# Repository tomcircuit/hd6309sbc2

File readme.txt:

This information pertains to the HD6309 Singleboard Computer v2.0

The HD6309 SBC II is a retroputing distraction, motivated by the fun I had designing
and using my first HD6309 SBC project. This time around, I favored 'all mod cons' over
'old skool'. In contrast to the v1.0, this version loses the Zilog SCC and Zilog CIO
devices, expands RAM to 16MB and addressable ROM to 64K. The SD card interface is
retained, as is the more up-to-date I2C realtime clock. The heart of this SBC is an
Altera Cyclone IV FPGA, in which all of the glue logic and peripherals are implemented.
So, with vastly more logic capacity, easy to do UARTs, the SPI master, a more friendly
I2C master, a paged memory mapper, and whatever else springs to mind...  The 
'penalty' for this luxury is that of mixed voltage design - the CPU and clock signals 
are in a 5V domain, everything else is in the 3.3V domain. A 5V DC/DC supplies the
CPU. Four octal transceivers shift the TTL signalling to LV-TTL. Sure, I could have 
put the CPU core in the FPGA, but no CPU just seems a bit like 'cheating'.
LOL, to each their own :-)  The SBC v2 is also physically smaller than its v1.0 
predecessor; measures 100 x 120mm.

I devised a stacking 64-pin connector scheme so that the FPGA board, the CPU board,
and an I/O board can all be used together. I have also spec'd out a 65C816 CPU board,
and a MC68HC000 board.

Firmware wise, I'll keep the rudimentary monitor, NoICE support, and the ROM-resident 
6809 MICROSOFT BASIC interpreter which I implemented on v1.0 (the latter is courtesty 
of Grant Searle). 

More up-to-date information on the SBC can be found on the Hackaday project page:
https://hackaday.io/project/173401-hd6309-singleboard-computer-ii

This work is licensed under the Creative Commons Attribution-ShareAlike 4.0 International License. 
To view a copy of this license, visit http://creativecommons.org/licenses/by-sa/4.0/.

HD6309 Singleboard Computer II
Tom LeMense
9/17/2024

tomcircuit@gmail.com
@TomLeMense

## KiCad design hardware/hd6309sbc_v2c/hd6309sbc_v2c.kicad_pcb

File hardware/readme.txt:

This set of design files implements the Schematic and PCB for the HD6309 Singleboard Computer II

Design tool is KiCad 5.1.6

PCB was designed with one-off production in mind, and to my own set of (largely unwritten) PCB
design rules. The board is double sided 100 x 120mm, with 8/8 track/spacing (mils), and 0.4mm minimum
hole size. The two most complicated components to solder are the EQPF144 MAX10 CPLD and the QFN28
CP2105 USB bridge. The rest of the components are fairly straightforward to assemble.

PDF of the PCB and Schematic can be found in the "plots" directory.
Gerber and drill information can be found in the "fabrication" directory.

My PCBs were fabricated by PCBway https://www.pcbway.com/ and I chose 1.6mm FR4 with ENIG surface 
treatment to make fine-pitch SMD soldering easier. I had a polyamide stencil manufactured by OSHstencils
https://www.oshstencils.com/. This will be my first foray with solder stencil, hotplate, and hot air
soldering. It's long overdue, because so many components simply cannot be reliably hand-soldered anymore.

More up-to-date information on the SBC can be found on the Hackaday project page:
https://hackaday.io/project/173401-hd6309-singleboard-computer-ii

This work is licensed under the Creative Commons Attribution-ShareAlike 4.0 International License. 
To view a copy of this license, visit http://creativecommons.org/licenses/by-sa/4.0/.

HD6309 Singleboard Computer II
Tom LeMense
7/8/2020

tomcircuit@gmail.com
@TomLeMense

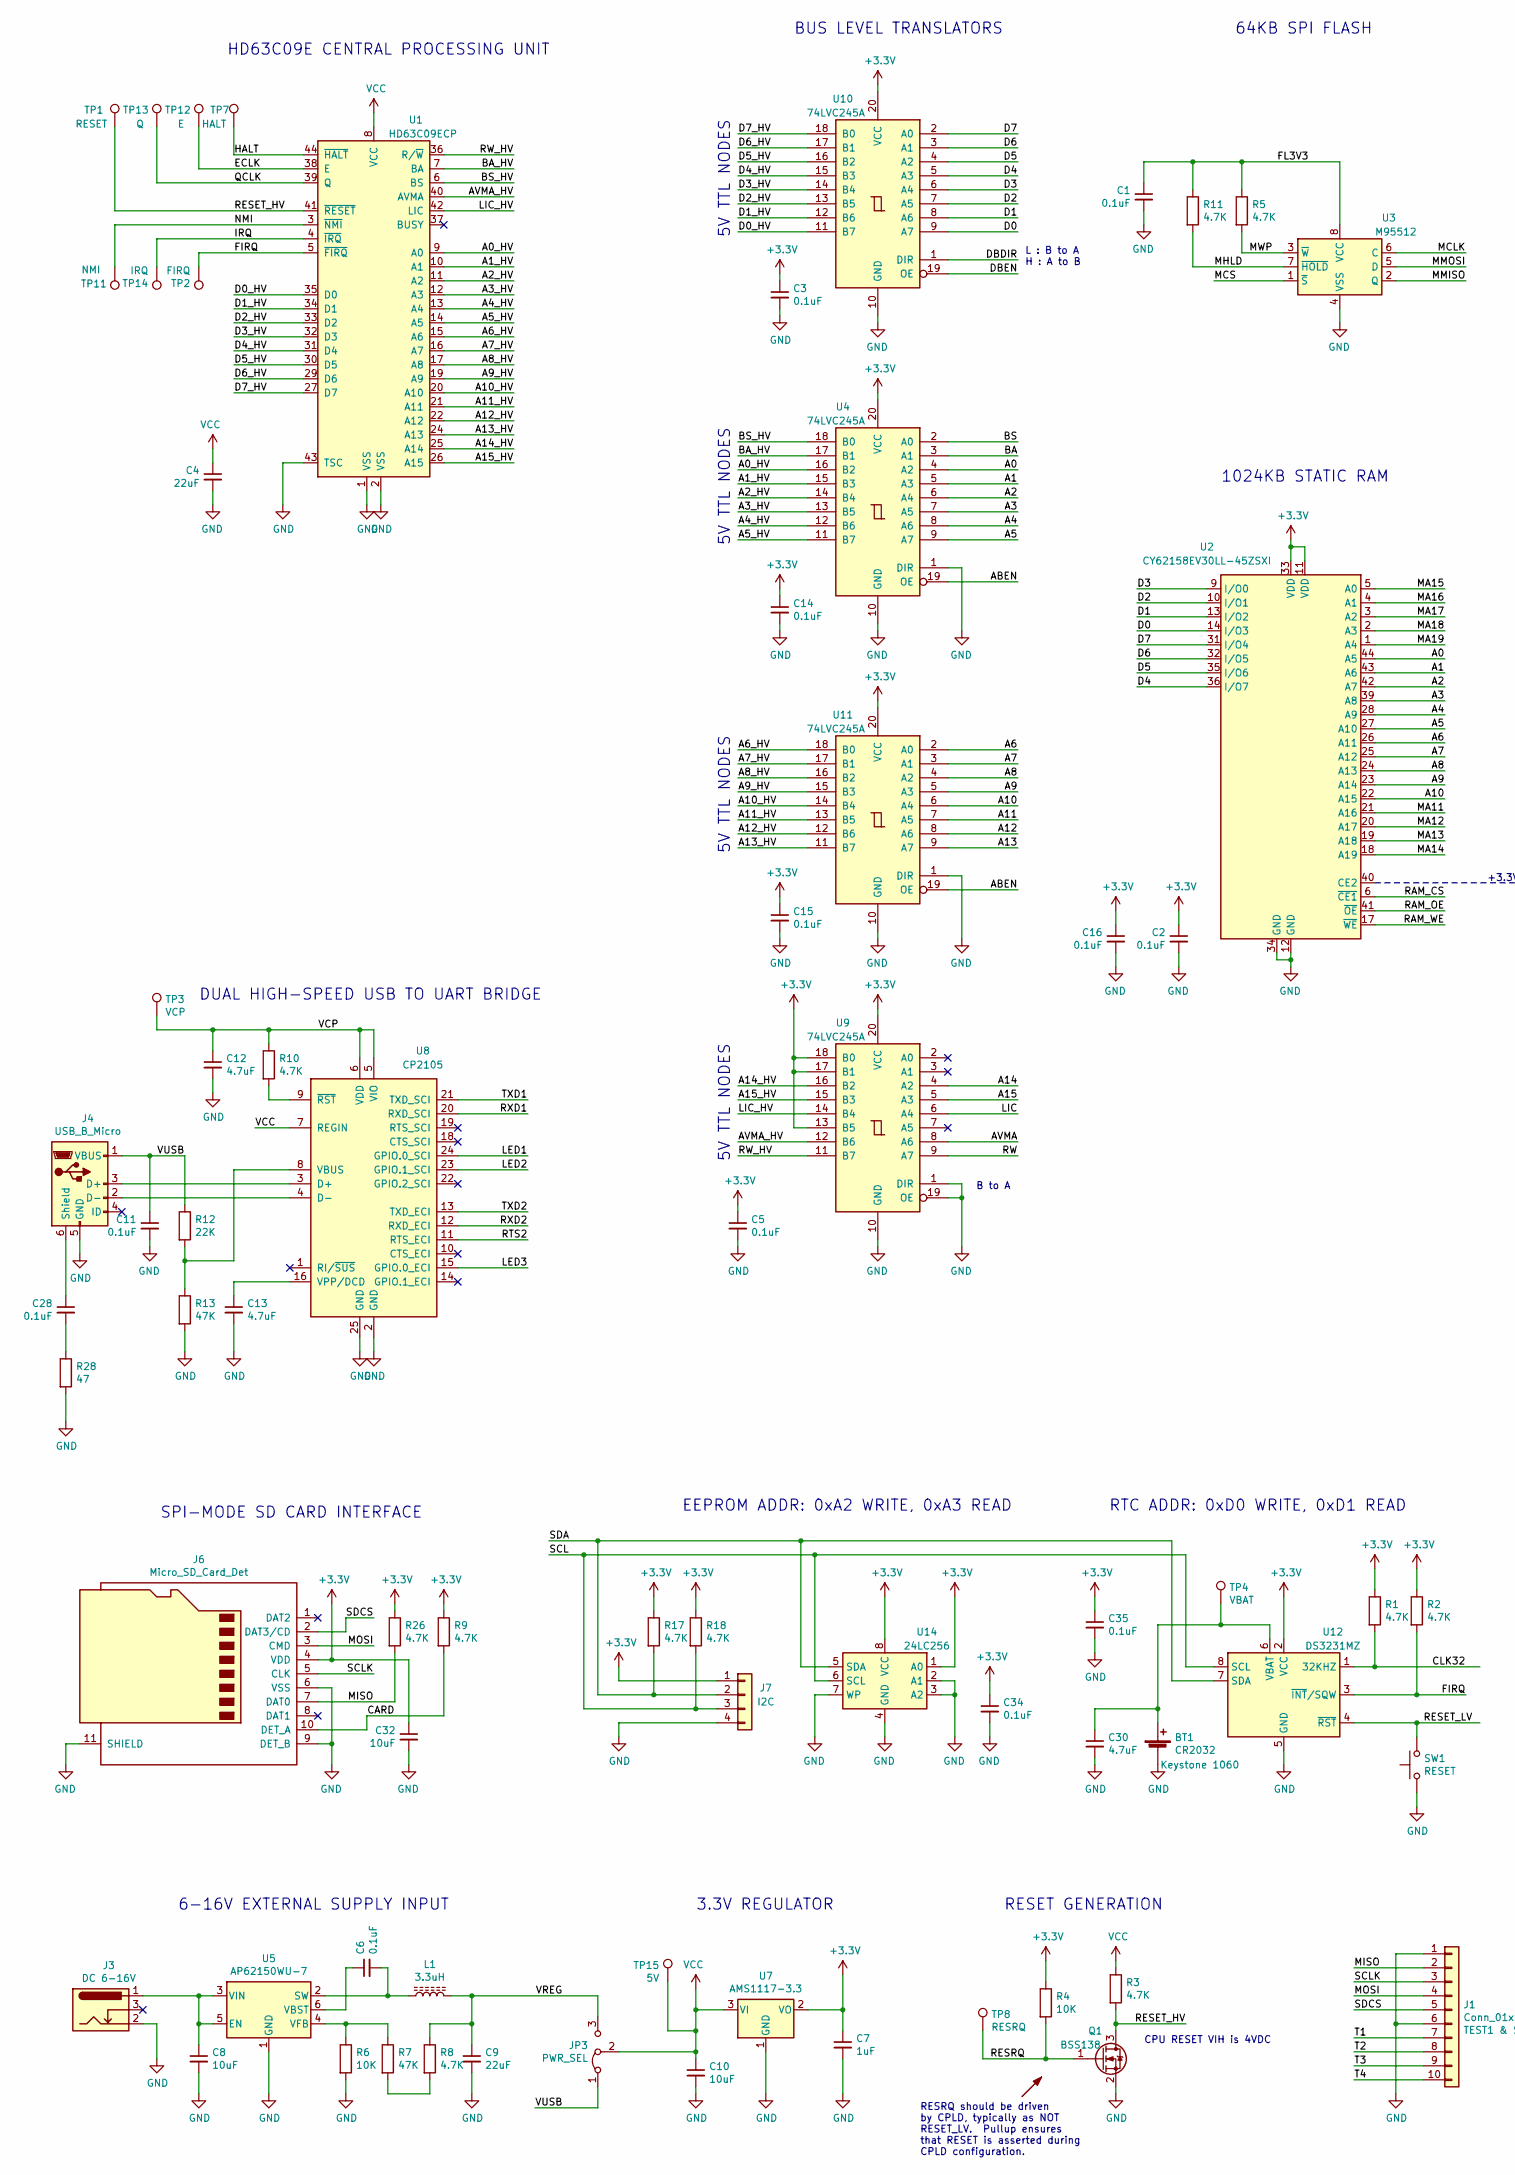
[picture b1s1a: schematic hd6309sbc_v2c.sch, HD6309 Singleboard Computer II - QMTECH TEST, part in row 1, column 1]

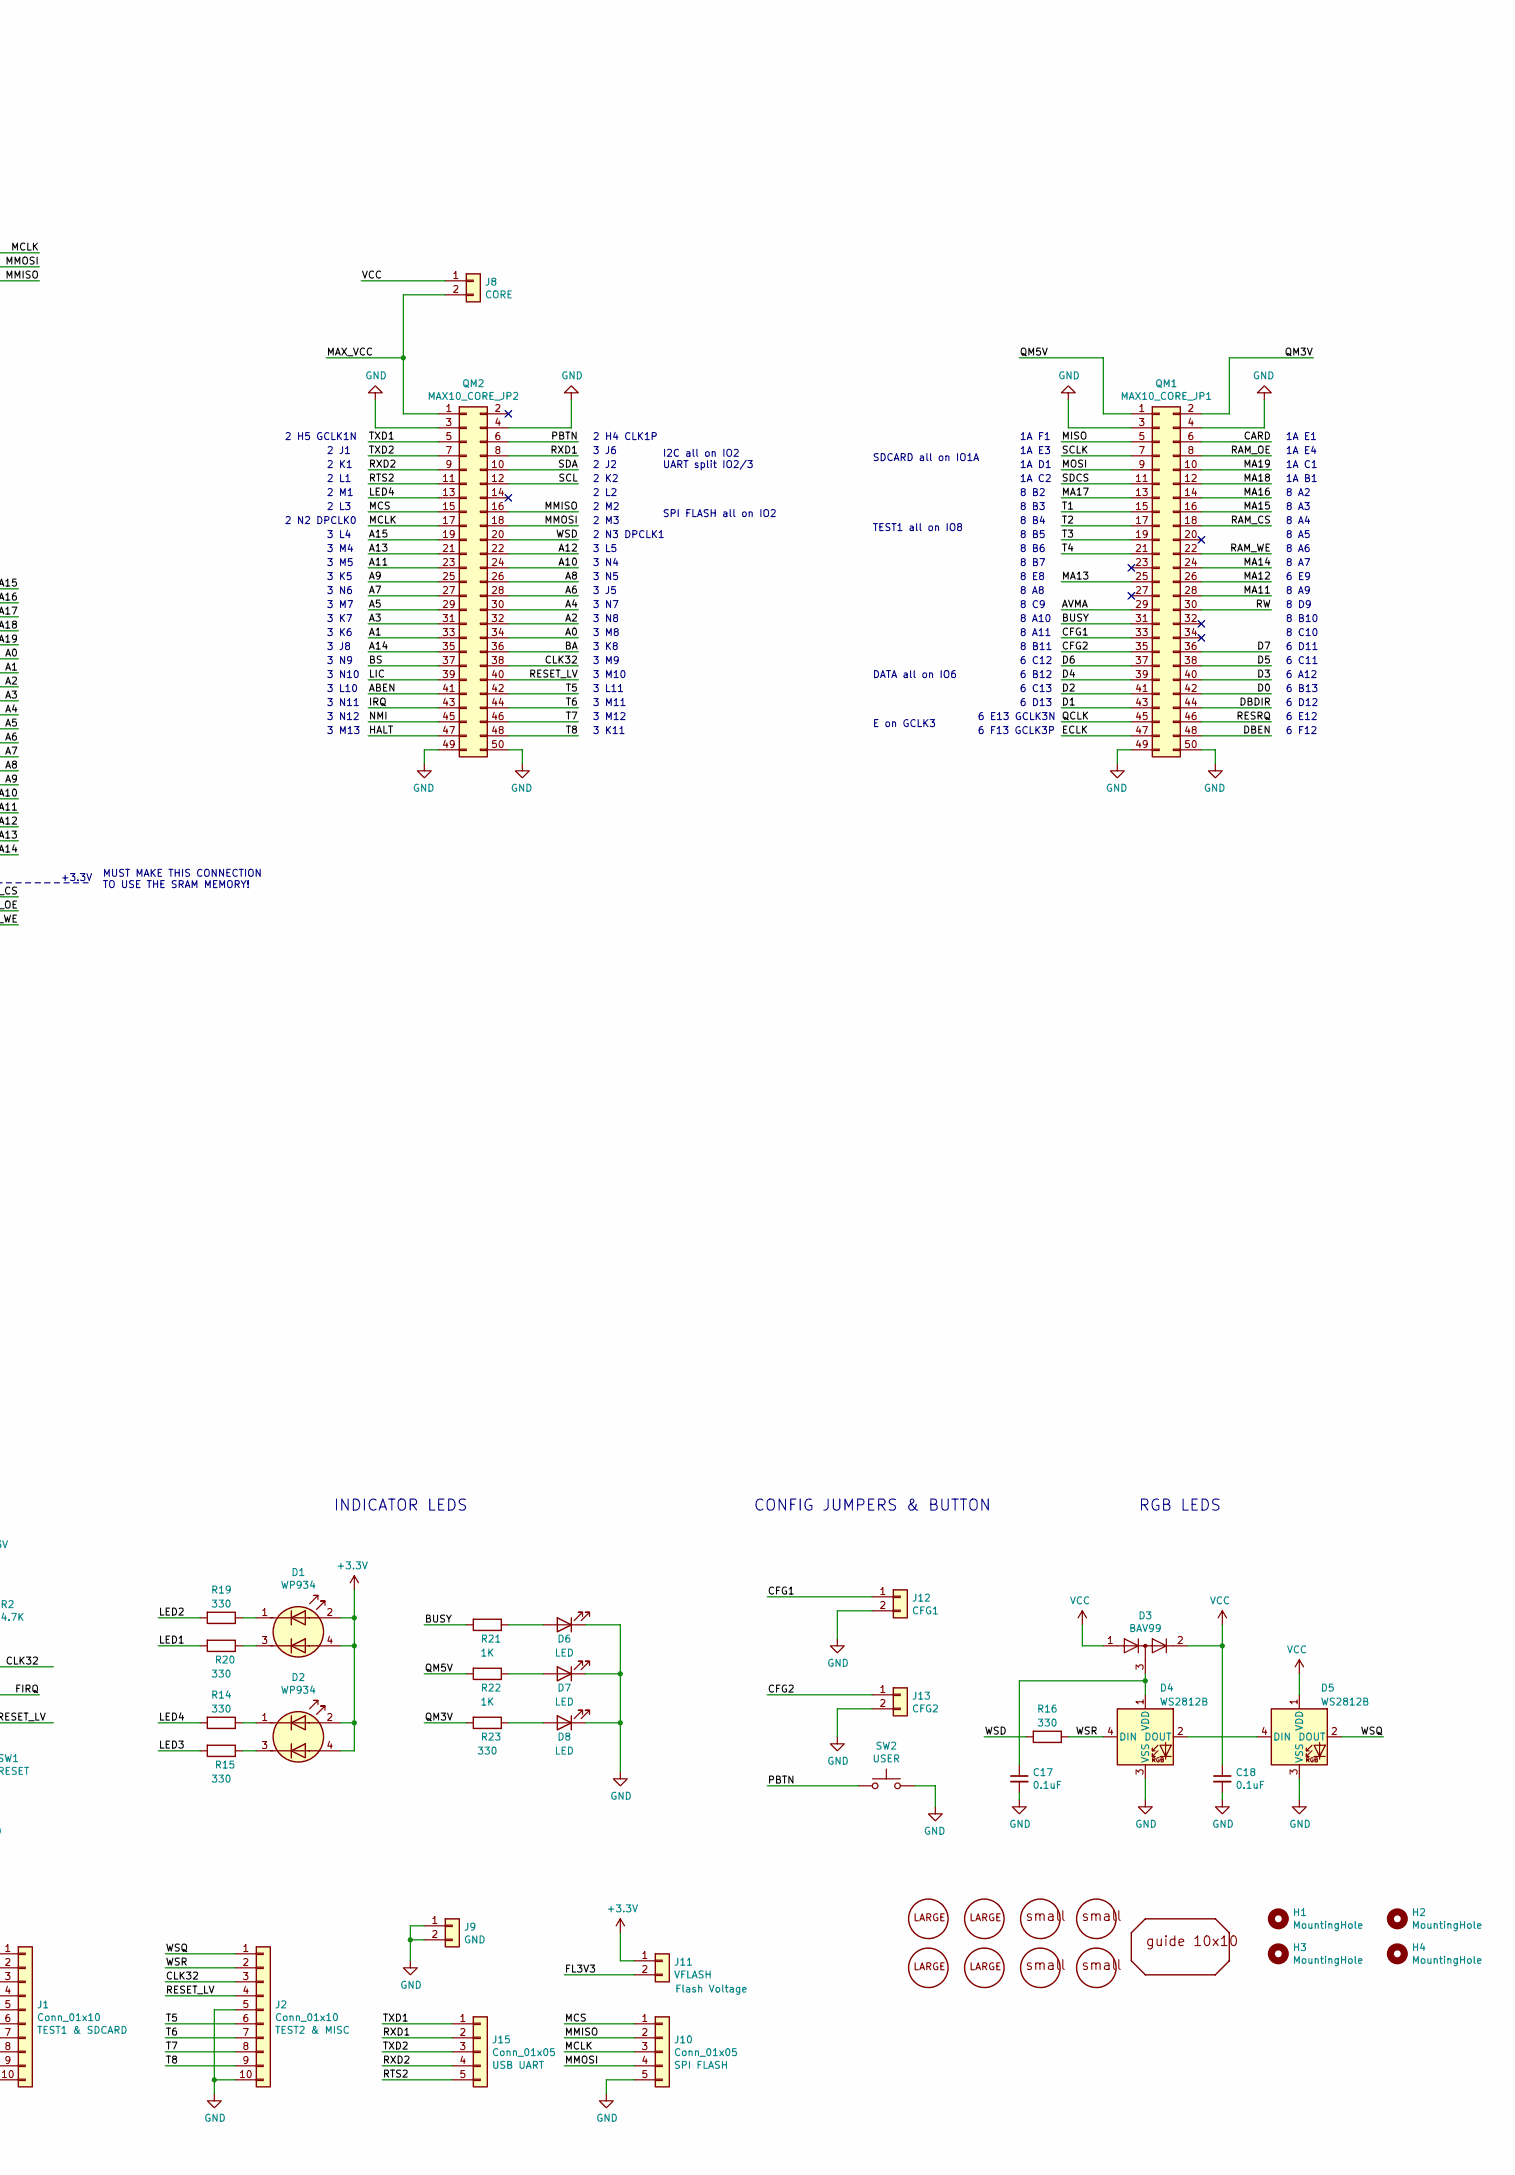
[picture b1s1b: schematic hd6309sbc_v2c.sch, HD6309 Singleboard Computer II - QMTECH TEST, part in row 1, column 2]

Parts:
BT1: CR2032; BatteryHolder_Keystone_1060_1x2032; MPN Keystone 1060
C1, C2, C3, C5, C6, C11, C14, C15, C16, C17, C18, C28, C34, C35: 0.1uF; C_0805_2012Metric
C4, C9: 22uF; C_0805_2012Metric
C7: 1uF; C_0805_2012Metric
C8: 10uF; C_1210_3225Metric_Pad1.33x2.70mm_HandSolder; MPN GRM32DR61E106KA12L
C10, C32: 10uF; C_0805_2012Metric
C12, C13, C30: 4.7uF; C_0805_2012Metric
D1, D2: WP934; 2GD
D3: BAV99; SOT-23
D4, D5: WS2812B; LED_WS2812B_PLCC4_5.0x5.0mm_P3.2mm
D6, D7, D8: LED; LED_0805_2012Metric_Pad1.15x1.40mm_HandSolder
H1, H2, H3, H4: MountingHole; MountingHole_4.3mm_M4_DIN965
J1, J2: Conn_01x10; PinHeader_1x10_P2.54mm_Vertical
J3: DC 6-16V; BarrelJack_CUI_PJ-102AH_Horizontal
J4: USB_B_Micro; USB_Micro-B_Wuerth_629105150521
J6: Micro_SD_Card_Det; microSD_HC_Hirose_DM3D-SF
J7: I2C; PinHeader_1x04_P2.54mm_Vertical
J8: CORE; PinHeader_1x02_P2.54mm_Vertical
J9: GND; PinHeader_1x02_P2.54mm_Vertical
J10, J15: Conn_01x05; PinHeader_1x05_P2.54mm_Vertical
J11: VFLASH; PinHeader_1x02_P2.54mm_Vertical
J12: CFG1; PinHeader_1x02_P2.54mm_Vertical
J13: CFG2; PinHeader_1x02_P2.54mm_Vertical
JP3: PWR_SEL; PinHeader_1x03_P2.54mm_Vertical
L1: 3.3uH; L_Wuerth_HCI-7040
Q1: BSS138; SOT-23
QM1: MAX10_CORE_JP1; PinHeader_2x25_P2.54mm_Vertical
QM2: MAX10_CORE_JP2; PinHeader_2x25_P2.54mm_Vertical
R1, R2, R3, R5, R8, R9, R10, R11, R17, R18, R26: 4.7K; R_0805_2012Metric
R4, R6: 10K; R_0805_2012Metric
R7, R13: 47K; R_0805_2012Metric
R12: 22K; R_0805_2012Metric
R14, R15, R16, R19, R20, R23: 330; R_0805_2012Metric
R21, R22: 1K; R_0805_2012Metric
R28: 47; R_0805_2012Metric
RG1: GUIDE_10X10; BOARD_10X10
RL1, RL2, RL3, RL4: PIN_LARGE_SINGLE_DEVICE; PIN_LARGE_SINGLE
RS1, RS2, RS3, RS4: PIN_SMALL_SINGLE_DEVICE; PIN_SMALL_SINGLE
SW1: RESET; SW_Tactile_SPST_Angled_PTS645Vx58-2LFS
SW2: USER; SW_Tactile_SPST_Angled_PTS645Vx58-2LFS
TP1: RESET; TestPoint_THTPad_2.0x2.0mm_Drill1.0mm
TP2: FIRQ; TestPoint_THTPad_2.0x2.0mm_Drill1.0mm
TP3: VCP; TestPoint_Pad_D1.5mm
TP4: VBAT; TestPoint_Pad_D1.5mm
TP7: HALT; TestPoint_THTPad_2.0x2.0mm_Drill1.0mm
TP8: RESRQ; TestPoint_THTPad_2.0x2.0mm_Drill1.0mm
TP11: NMI; TestPoint_THTPad_2.0x2.0mm_Drill1.0mm
TP12: E; TestPoint_THTPad_2.0x2.0mm_Drill1.0mm
TP13: Q; TestPoint_THTPad_2.0x2.0mm_Drill1.0mm
TP14: IRQ; TestPoint_THTPad_2.0x2.0mm_Drill1.0mm
TP15: 5V; TestPoint_THTPad_2.0x2.0mm_Drill1.0mm
U1: HD63C09ECP; PLCC-44
U2: CY62158EV30LL-45ZSXI; TSOP-II-44_10.16x18.41mm_P0.8mm
U3: M95512; SOIC-8_3.9x4.9mm_P1.27mm
U4, U9, U10, U11: 74LVC245A; TSSOP-20_4.4x6.5mm_P0.65mm
U5: AP62150WU-7; SOT-23-6
U7: AMS1117-3.3; SOT-223-3_TabPin2
U8: CP2105; QFN-24-1EP_4x4mm_P0.5mm_EP2.6x2.6mm
U12: DS3231MZ; SO-8_3.9x4.9mm_P1.27mm
U14: 24LC256; SO-8_3.9x4.9mm_P1.27mm

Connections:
+3V3: C2.1, C3.1, C5.1, C7.1, C14.1, C15.1, C16.1, C32.1, C34.1, C35.1, D1.2 (K1), D1.4 (K2), D2.2 (K1), D2.4 (K2), J6.4 (VDD), J7.1, J11.1, R1.1, R2.1, R4.1, R9.1, R17.1, R18.1, R26.1, U2.11 (VDD), U2.33 (VDD), U4.20 (VCC), U7.2 (VO), U9.13 (B5), U9.17 (B1), U9.18 (B0), U9.20 (VCC), U10.20 (VCC), U11.20 (VCC), U12.2 (VCC), U14.1 (A0), U14.8 (VCC)
/A0: QM2.34, U2.44 (A5), U4.4 (A2)
/A0_HV: U1.9 (A0), U4.16 (B2)
/A1: QM2.33, U2.43 (A6), U4.5 (A3)
/A1_HV: U1.10 (A1), U4.15 (B3)
/A2: QM2.32, U2.42 (A7), U4.6 (A4)
/A2_HV: U1.11 (A2), U4.14 (B4)
/A3: QM2.31, U2.39 (A8), U4.7 (A5)
/A3_HV: U1.12 (A3), U4.13 (B5)
/A4: QM2.30, U2.28 (A9), U4.8 (A6)
/A4_HV: U1.13 (A4), U4.12 (B6)
/A5: QM2.29, U2.27 (A10), U4.9 (A7)
/A5_HV: U1.14 (A5), U4.11 (B7)
/A6: QM2.28, U2.26 (A11), U11.2 (A0)
/A6_HV: U1.15 (A6), U11.18 (B0)
/A7: QM2.27, U2.25 (A12), U11.3 (A1)
/A7_HV: U1.16 (A7), U11.17 (B1)
/A8: QM2.26, U2.24 (A13), U11.4 (A2)
/A8_HV: U1.17 (A8), U11.16 (B2)
/A9: QM2.25, U2.23 (A14), U11.5 (A3)
/A9_HV: U1.19 (A9), U11.15 (B3)
/A10: QM2.24, U2.22 (A15), U11.6 (A4)
/A10_HV: U1.20 (A10), U11.14 (B4)
/A11: QM2.23, U11.7 (A5)
/A11_HV: U1.21 (A11), U11.13 (B5)
/A12: QM2.22, U11.8 (A6)
/A12_HV: U1.22 (A12), U11.12 (B6)
/A13: QM2.21, U11.9 (A7)
/A13_HV: U1.24 (A13), U11.11 (B7)
/A14: QM2.35, U9.4 (A2)
/A14_HV: U1.25 (A14), U9.16 (B2)
/A15: QM2.19, U9.5 (A3)
/A15_HV: U1.26 (A15), U9.15 (B3)
/ABEN: QM2.41, U4.19 (OE), U11.19 (OE)
/AVMA: QM1.29, U9.8 (A6)
/AVMA_HV: U1.40 (AVMA), U9.12 (B6)
/BA: QM2.36, U4.3 (A1)
/BA_HV: U1.7 (BA), U4.17 (B1)
/BS: QM2.37, U4.2 (A0)
/BS_HV: U1.6 (BS), U4.18 (B0)
/BUSY: QM1.31, R21.2
/CARD: J6.10 (DET_A), QM1.6, R9.2
/CFG1: J12.1, QM1.33
/CFG2: J13.1, QM1.35
/CLK32: J2.3, QM2.38, R1.2, U12.1 (32KHZ)
/D0: QM1.42, U2.14 (I/O3), U10.9 (A7)
/D0_HV: U1.35 (D0), U10.11 (B7)
/D1: QM1.43, U2.13 (I/O2), U10.8 (A6)
/D1_HV: U1.34 (D1), U10.12 (B6)
/D2: QM1.41, U2.10 (I/O1), U10.7 (A5)
/D2_HV: U1.33 (D2), U10.13 (B5)
/D3: QM1.40, U2.9 (I/O0), U10.6 (A4)
/D3_HV: U1.32 (D3), U10.14 (B4)
/D4: QM1.39, U2.36 (I/O7), U10.5 (A3)
/D4_HV: U1.31 (D4), U10.15 (B3)
/D5: QM1.38, U2.35 (I/O6), U10.4 (A2)
/D5_HV: U1.30 (D5), U10.16 (B2)
/D6: QM1.37, U2.32 (I/O5), U10.3 (A1)
/D6_HV: U1.29 (D6), U10.17 (B1)
/D7: QM1.36, U2.31 (I/O4), U10.2 (A0)
/D7_HV: U1.27 (D7), U10.18 (B0)
/DBDIR: QM1.44, U10.1 (DIR)
/DBEN: QM1.48, U10.19 (OE)
/ECLK: QM1.47, TP12.1, U1.38 (E)
/FIRQ: R2.2, TP2.1, U1.5 (~FIRQ), U12.3 (~INT~/SQW)
/FL3V3: C1.1, J11.2, R5.1, R11.1, U3.8 (VCC)
/HALT: QM2.47, TP7.1, U1.44 (~HALT)
/IRQ: QM2.43, TP14.1, U1.4 (~IRQ)
/LED1: R20.2, U8.24 (GPIO.0_SCI)
/LED2: R19.2, U8.23 (GPIO.1_SCI)
/LED3: R15.2, U8.15 (GPIO.0_ECI)
/LED4: QM2.13, R14.2
/LIC: QM2.39, U9.6 (A4)
/LIC_HV: U1.42 (LIC), U9.14 (B4)
/MA11: QM1.28, U2.21 (A16)
/MA12: QM1.26, U2.20 (A17)
/MA13: QM1.25, U2.19 (A18)
/MA14: QM1.24, U2.18 (A19)
/MA15: QM1.16, U2.5 (A0)
/MA16: QM1.14, U2.4 (A1)
/MA17: QM1.13, U2.3 (A2)
/MA18: QM1.12, U2.2 (A3)
/MA19: QM1.10, U2.1 (A4)
/MAX_VCC: J8.2, QM2.1
/MCLK: J10.3, QM2.17, U3.6 (C)
/MCS: J10.1, QM2.15, U3.1 (~S)
/MHLD: R11.2, U3.7 (~HOLD)
/MISO: J1.2, J6.7 (DAT0), QM1.5, R26.2
/MMISO: J10.2, QM2.16, U3.2 (Q)
/MMOSI: J10.4, QM2.18, U3.5 (D)
/MOSI: J1.4, J6.3 (CMD), QM1.9
/MWP: R5.2, U3.3 (~W)
/NMI: QM2.45, TP11.1, U1.3 (~NMI)
/PBTN: QM2.6, SW2.1
/QCLK: QM1.45, TP13.1, U1.39 (Q)
/QM3V: QM1.2, R23.2
/QM5V: QM1.1, R22.2
/RAM_CS: QM1.18, U2.6 (~CE1)
/RAM_OE: QM1.8, U2.41 (~OE)
/RAM_WE: QM1.22, U2.17 (~WE)
/RESET_HV: Q1.3 (D), R3.2, TP1.1, U1.41 (~RESET)
/RESET_LV: J2.4, QM2.40, SW1.2, U12.4 (~RST)
/RESRQ: Q1.1 (G), QM1.46, R4.2, TP8.1
/RTS2: J15.5, QM2.11, U8.11 (RTS_ECI)
/RW: QM1.30, U9.9 (A7)
/RW_HV: U1.36 (R/~W), U9.11 (B7)
/RXD1: J15.2, QM2.8, U8.20 (RXD_SCI)
/RXD2: J15.4, QM2.9, U8.12 (RXD_ECI)
/SCL: J7.3, QM2.12, R18.2, U12.8 (SCL), U14.6 (SCL)
/SCLK: J1.3, J6.5 (CLK), QM1.7
/SDA: J7.2, QM2.10, R17.2, U12.7 (SDA), U14.5 (SDA)
/SDCS: J1.5, J6.2 (DAT3/CD), QM1.11
/T1: J1.7, QM1.15
/T2: J1.8, QM1.17
/T3: J1.9, QM1.19
/T4: J1.10, QM1.21
/T5: J2.6, QM2.42
/T6: J2.7, QM2.44
/T7: J2.8, QM2.46
/T8: J2.9, QM2.48
/TXD1: J15.1, QM2.5, U8.21 (TXD_SCI)
/TXD2: J15.3, QM2.7, U8.13 (TXD_ECI)
/VCP: C12.1, R10.1, TP3.1, U8.5 (VIO), U8.6 (VDD)
/VREG: C9.1, JP3.3 (B), L1.2, R8.1
/VUSB: C11.1, J4.1 (VBUS), JP3.1 (A), R12.1
/WSD: QM2.20, R16.2
/WSQ: D5.2 (DOUT), J2.1
/WSR: D4.4 (DIN), J2.2, R16.1
GND: BT1.2 (-), C1.2, C2.2, C3.2, C4.2, C5.2, C7.2, C8.2, C9.2, C10.2, C11.2, C12.2, C13.2, C14.2, C15.2, C16.2, C17.2, C18.2, C30.2, C32.2, C34.2, C35.2, D4.3 (VSS), D5.3 (VSS), D6.1 (K), D7.1 (K), D8.1 (K), J1.1, J1.6, J2.5, J2.10, J3.2, J4.5 (GND), J6.6 (VSS), J6.9 (DET_B), J6.11 (SHIELD), J7.4, J9.1, J9.2, J10.5, J12.2, J13.2, Q1.2 (S), QM1.3, QM1.4, QM1.49, QM1.50, QM2.3, QM2.4, QM2.49, QM2.50, R6.2, R13.2, R28.2, SW1.1, SW2.2, U1.1 (VSS), U1.2 (VSS), U1.43 (TSC), U2.12 (GND), U2.34 (GND), U3.4 (VSS), U4.1 (DIR), U4.10 (GND), U5.1 (GND), U7.1 (GND), U8.2 (GND), U8.25 (GND), U9.1 (DIR), U9.10 (GND), U9.19 (OE), U10.10 (GND), U11.1 (DIR), U11.10 (GND), U12.5 (GND), U14.2 (A1), U14.3 (A2), U14.4 (GND), U14.7 (WP)
unnamed: BT1.1 (+), C30.1, TP4.1, U12.6 (VBAT)
unnamed: C6.1, U5.6 (VBST)
unnamed: C6.2, L1.1, U5.2 (SW)
unnamed: C8.1, J3.1, U5.3 (VIN), U5.5 (EN)
unnamed: C13.1, U8.16 (VPP/DCD)
unnamed: C17.1, D3.3 (K), D4.1 (VDD)
unnamed: C28.1, J4.6 (Shield)
unnamed: C28.2, R28.1
unnamed: D1.1 (A1), R19.1
unnamed: D1.3 (A2), R20.1
unnamed: D2.1 (A1), R14.1
unnamed: D2.3 (A2), R15.1
unnamed: D4.2 (DOUT), D5.4 (DIN)
unnamed: D6.2 (A), R21.1
unnamed: D7.2 (A), R22.1
unnamed: D8.2 (A), R23.1
unnamed: J4.2 (D-), U8.4 (D-)
unnamed: J4.3 (D+), U8.3 (D+)
unnamed: R6.1, R7.1, U5.4 (VFB)
unnamed: R7.2, R8.2
unnamed: R10.2, U8.9 (~RST)
unnamed: R12.2, R13.1, U8.8 (VBUS)
VCC: C4.1, C10.1, C18.1, D3.1 (K), D3.2 (A), D5.1 (VDD), J8.1, JP3.2 (C), R3.1, TP15.1, U1.8 (VCC), U7.3 (VI), U8.7 (REGIN)

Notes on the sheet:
6-16V EXTERNAL SUPPLY INPUT
3.3V REGULATOR
DUAL HIGH-SPEED USB TO UART BRIDGE
RTC ADDR: 0xD0 WRITE, 0xD1 READ
EEPROM ADDR: 0xA2 WRITE, 0xA3 READ
SPI-MODE SD CARD INTERFACE
5V TTL NODES
INDICATOR LEDS
RGB LEDS
RESRQ should be driven by CPLD, typically as NOT RESET_LV. Pullup ensures that RESET is asserted during CPLD configuration.
HD63C09E CENTRAL PROCESSING UNIT
1024KB STATIC RAM
BUS LEVEL TRANSLATORS
CPU RESET VIH is 4VDC
RESET GENERATION
B to A
L : B to A H : A to B
64KB SPI FLASH
1A F1
1A E3
1A D1
1A C2
8 B2
8 B3
8 B4
8 B5
8 B6
8 E8
8 C9
8 A10
8 A11
8 B11
6 C12
8 A8
6 B12
6 C13
6 F13 GCLK3P
6 E13 GCLK3N
6 E12
6 F12

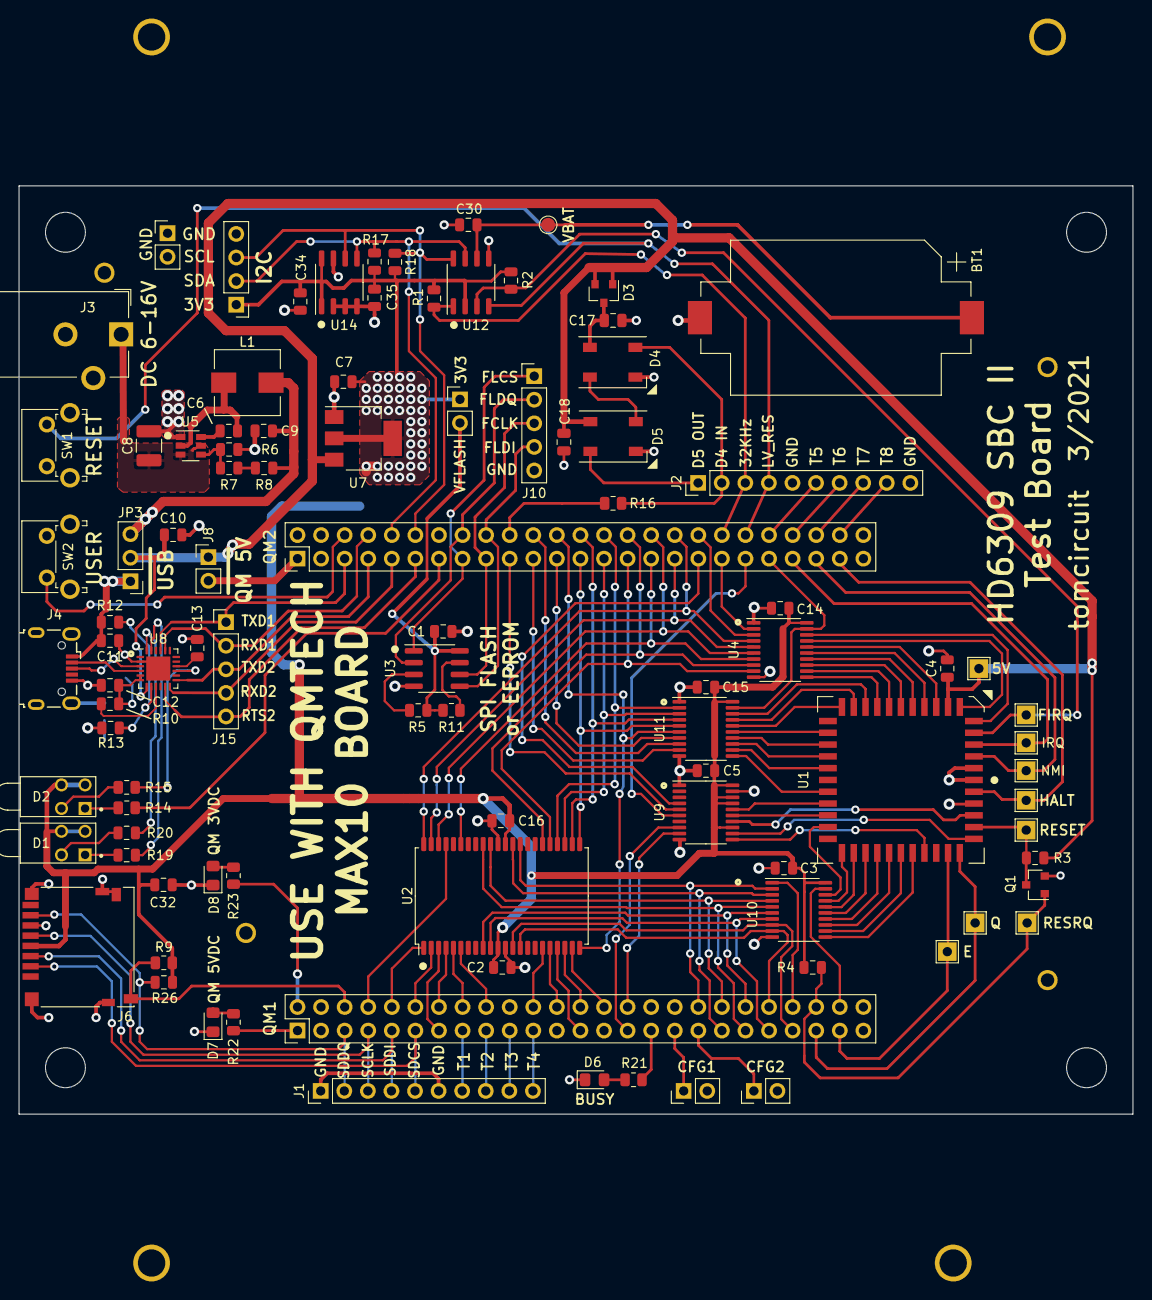
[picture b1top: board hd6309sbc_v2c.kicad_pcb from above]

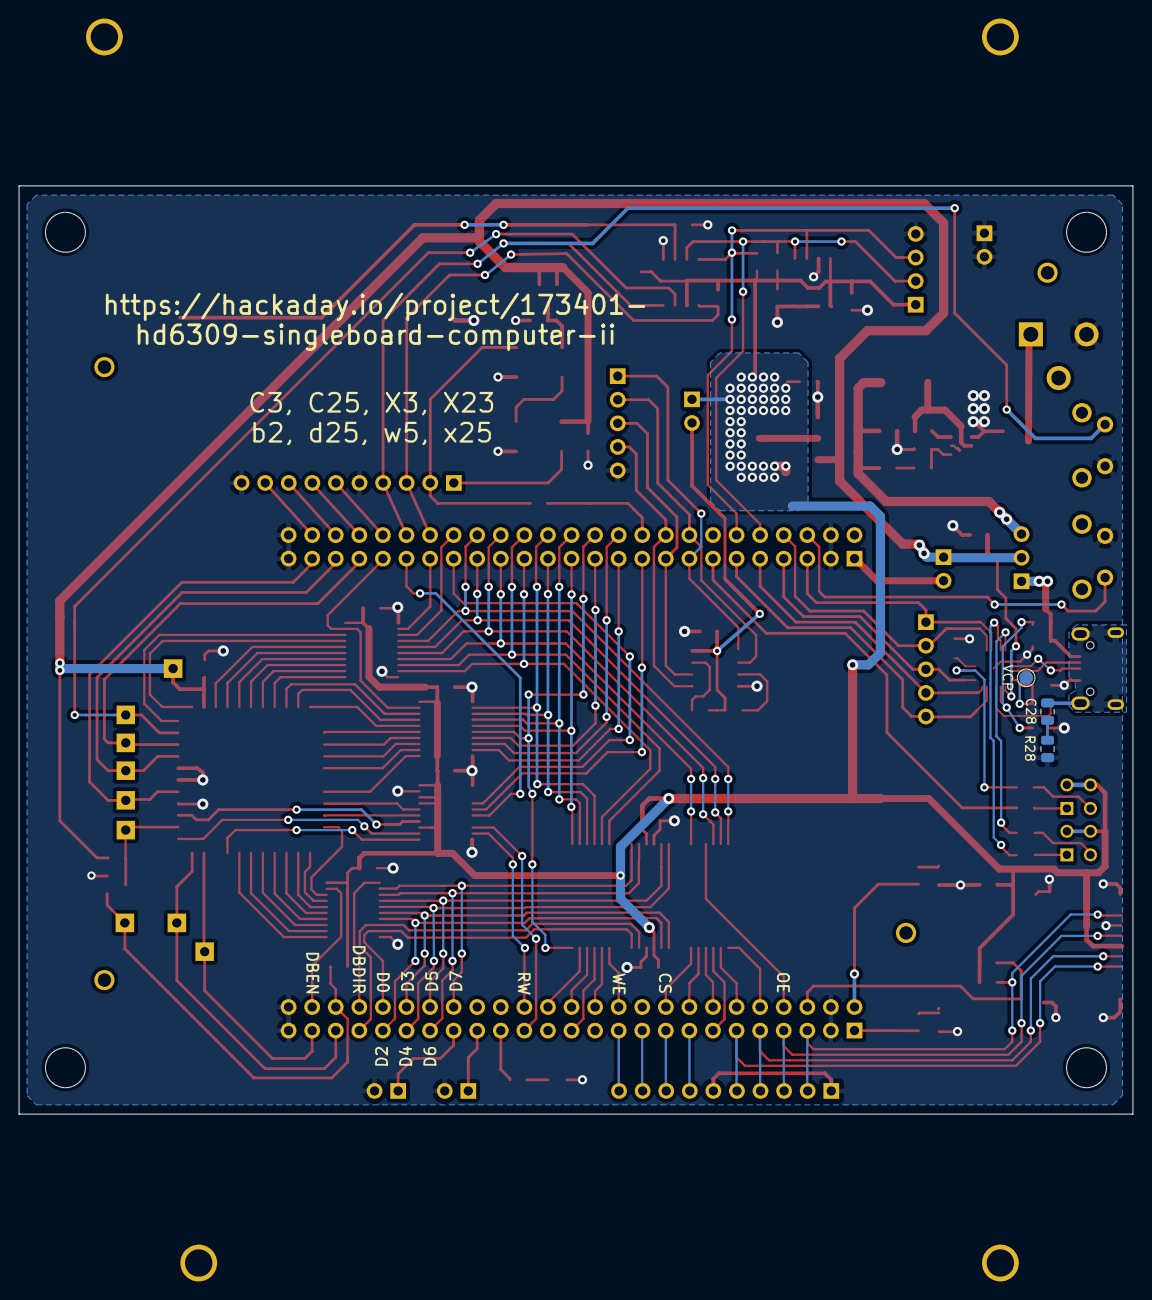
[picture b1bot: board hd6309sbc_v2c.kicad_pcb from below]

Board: 2 copper layers, 120.0 x 100.0 mm, 113 parts (3 on the bottom side), 152 nets.
